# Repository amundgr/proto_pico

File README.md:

# proto_pico
A mash of several different projects in one PCB in an attempt to kickstart all of them at once. Why fail and give up on one project when you can do it on several at once!

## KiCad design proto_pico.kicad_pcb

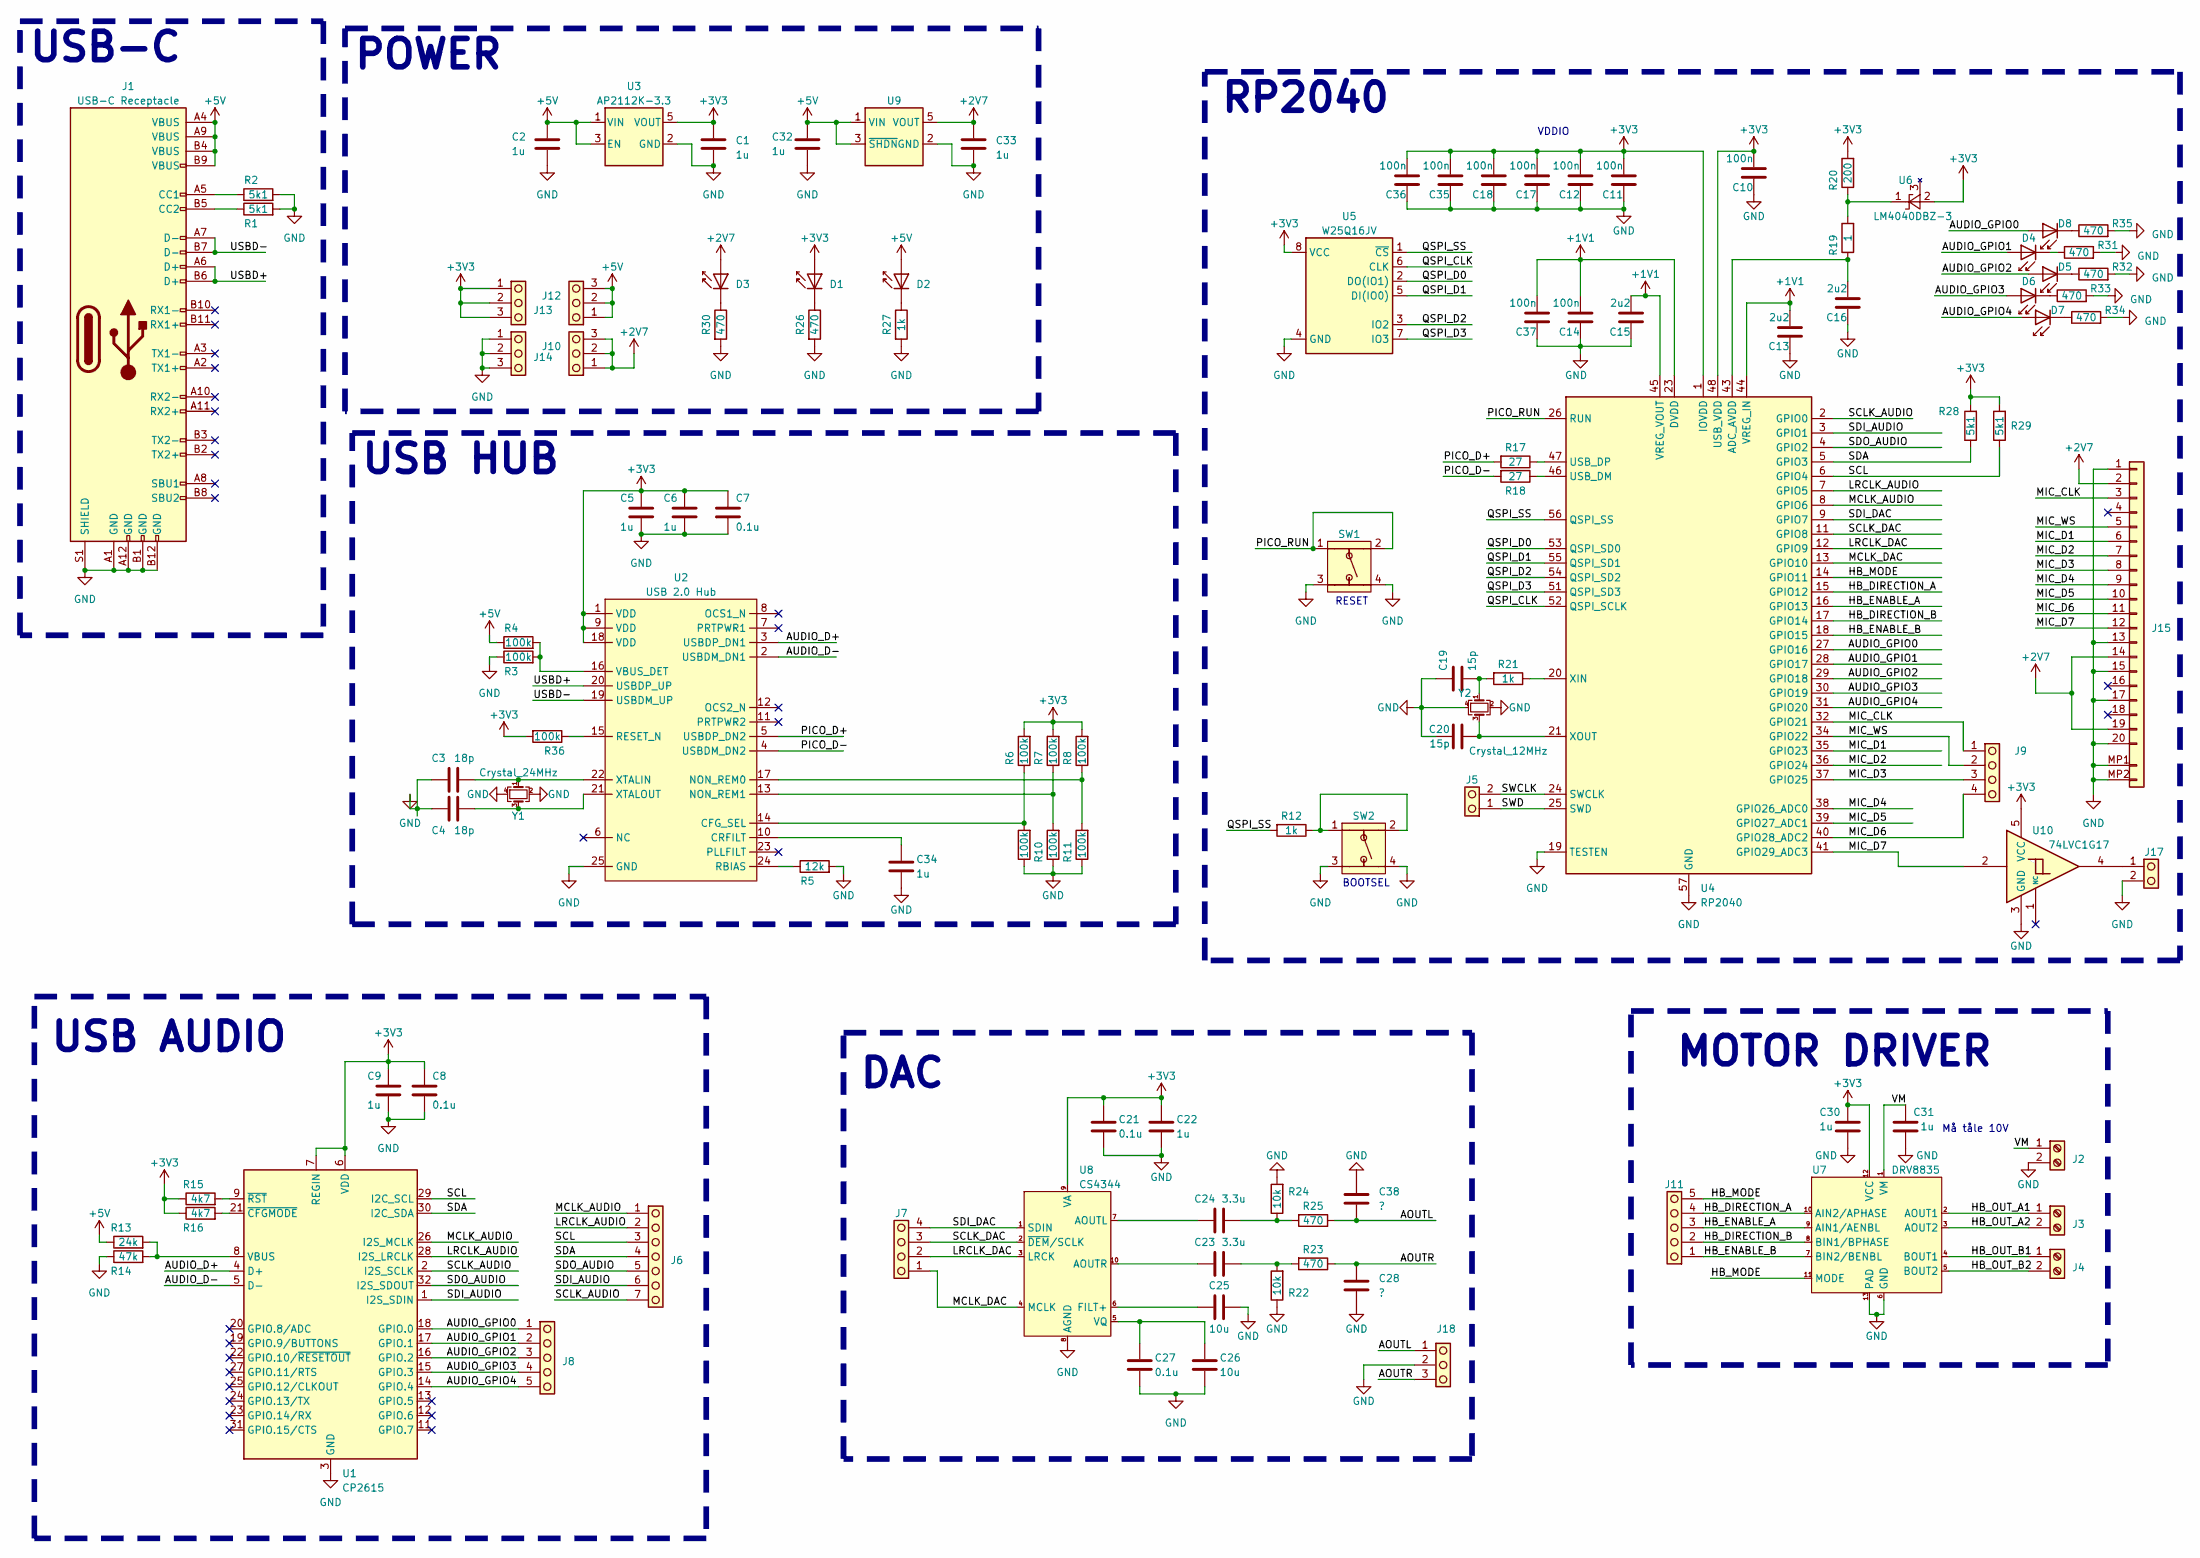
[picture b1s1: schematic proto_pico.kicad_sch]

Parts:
C1, C2, C5, C6, C9, C22, C30, C31, C32, C33, C34: 1u; C_0603_1608Metric
C3, C4: 18p; C_0603_1608Metric
C7, C8, C21, C27: 0.1u; C_0603_1608Metric
C10, C11, C12, C14, C17, C18, C35, C36, C37: 100n; C_0603_1608Metric
C13, C15, C16: 2u2; C_0603_1608Metric
C19, C20: 15p; C_0603_1608Metric
C23, C24: 3.3u; C_0805_2012Metric
C25, C26: 10u; C_0805_2012Metric
C28, C38: ?; C_0805_2012Metric
D1, D2, D3, D4, D5, D6, D7, D8: LED_0603_1608Metric
J1: USB-C Receptacle; USB_C_Receptacle_Amphenol_12401610E4-2A
J2, J3, J4: Screw_Terminal_01x02; 2x1_screw_terminal
J5, J17: PinHeader_1x02_P2.54mm_Vertical
J6: Header_2.54mm_1x7; PinHeader_1x07_P2.54mm_Vertical
J7, J9: PinHeader_1x04_P2.54mm_Vertical
J8, J11: Header_2.54mm_1x5; PinHeader_1x05_P2.54mm_Vertical
J10, J12, J13, J14, J18: PinHeader_1x03_P2.54mm_Vertical
J15: FFC_20_Pin
R1, R2, R28, R29: 5k1; R_0603_1608Metric
R3, R4, R6, R7, R8, R9, R10, R11, R36: 100k; R_0603_1608Metric
R5: 12k; R_0603_1608Metric
R12, R21, R27: 1k; R_0603_1608Metric
R13: 24k; R_0603_1608Metric
R14: 47k; R_0603_1608Metric
R15, R16: 4k7; R_0603_1608Metric
R17, R18: 27; R_0603_1608Metric
R19: 1; R_0603_1608Metric
R20: 200; R_0603_1608Metric
R22, R24: 10k; R_0603_1608Metric
R23, R25, R26, R30, R31, R32, R33, R34, R35: 470; R_0603_1608Metric
SW1, SW2: PTS647
U1: CP2615; QFN-32-1EP_5x5mm_P0.5mm_EP3.3x3.3mm
U2: USB 2.0 Hub; QFN-24-1EP_4x4mm_P0.5mm_EP2.5x2.5mm
U3: AP2112K-3.3; SOT-23-5
U4: RP2040; QFN-56-1EP_7x7mm_P0.4mm_EP3.2x3.2mm
U5: W25Q16JV; SOIC-8_5.23x5.23mm_P1.27mm
U6: LM4040DBZ-3; SOT-23-3
U7: DRV8835; WSON-12-1EP_3x2mm_P0.5mm_EP1x2.65
U8: CS4344; MSOP-10_3x3mm_P0.5mm
U9: SOT-23-5
U10: 74LVC1G17; SOT-23-5
Y1: Crystal_24MHz; Crystal_SMD_SeikoEpson_FA128-4Pin_2.0x1.6mm
Y2: Crystal_12MHz; ECX-32

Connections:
+1V1: C13.2, C14.2, C15.2, C37.2, U4.23 (DVDD), U4.44 (VREG_IN), U4.45 (VREG_VOUT), U4.50 (DVDD)
+2V8: C33.1, D3.2 (A), J10.1, J10.2, J10.3, J15.2, J15.14, J15.19, U9.5 (VOUT)
+3V3: C1.1, C5.1, C6.1, C7.1, C8.1, C9.1, C10.2, C11.2, C12.2, C17.2, C18.2, C21.1, C22.1, C30.1, C35.2, C36.2, D1.2 (A), J13.1, J13.2, J13.3, R6.2, R7.2, R8.2, R15.1, R16.1, R20.2, R28.2, R29.2, R36.2, U1.6 (VDD), U1.7 (REGIN), U2.1 (VDD), U2.9 (VDD), U2.18 (VDD), U3.5 (VOUT), U4.1 (IOVDD), U4.10 (IOVDD), U4.22 (IOVDD), U4.33 (IOVDD), U4.42 (IOVDD), U4.48 (USB_VDD), U4.49 (IOVDD), U5.8 (VCC), U6.2 (A), U7.12 (VCC), U8.9 (VA), U10.5 (VCC)
+5V: C2.1, C32.1, D2.2 (A), J1.A4 (VBUS), J1.A9 (VBUS), J1.B4 (VBUS), J1.B9 (VBUS), J12.1, J12.2, J12.3, R4.1, R13.1, U3.1 (VIN), U3.3 (EN), U9.1 (VIN), U9.3 (~SHDN)
/AOUTL: C38.2, J18.1, R25.1
/AOUTR: C28.1, J18.3, R23.1
/AUDIO_D+: U1.4 (D+), U2.3 (USBDP_DN1)
/AUDIO_D-: U1.5 (D-), U2.2 (USBDM_DN1)
/AUDIO_GPIO0: D8.2 (A), J8.1, U1.18 (GPIO.0), U4.27 (GPIO16)
/AUDIO_GPIO1: D4.2 (A), J8.2, U1.17 (GPIO.1), U4.28 (GPIO17)
/AUDIO_GPIO2: D5.2 (A), J8.3, U1.16 (GPIO.2), U4.29 (GPIO18)
/AUDIO_GPIO3: D6.2 (A), J8.4, U1.15 (GPIO.3), U4.30 (GPIO19)
/AUDIO_GPIO4: D7.2 (A), J8.5, U1.14 (GPIO.4), U4.31 (GPIO20)
/HB_DIRECTION_A: J11.4, U4.15 (GPIO12), U7.10 (AIN2/APHASE)
/HB_DIRECTION_B: J11.2, U4.17 (GPIO14), U7.8 (BIN1/BPHASE)
/HB_ENABLE_A: J11.3, U4.16 (GPIO13), U7.9 (AIN1/AENBL)
/HB_ENABLE_B: J11.1, U4.18 (GPIO15), U7.7 (BIN2/BENBL)
/HB_MODE: J11.5, U4.14 (GPIO11), U7.11 (MODE)
/HB_OUT_A1: J3.1, U7.2 (AOUT1)
/HB_OUT_A2: J3.2, U7.3 (AOUT2)
/HB_OUT_B1: J4.1, U7.4 (BOUT1)
/HB_OUT_B2: J4.2, U7.5 (BOUT2)
/LRCLK_AUDIO: J6.2, U1.28 (I2S_LRCLK), U4.7 (GPIO5)
/LRCLK_DAC: J7.2, U4.12 (GPIO9), U8.3 (LRCK)
/MCLK_AUDIO: J6.1, U1.26 (I2S_MCLK), U4.8 (GPIO6)
/MCLK_DAC: J7.1, U4.13 (GPIO10), U8.4 (MCLK)
/MIC_CLK: J9.1, J15.3, U4.32 (GPIO21)
/MIC_D1: J15.6, U4.35 (GPIO23)
/MIC_D2: J15.7, U4.36 (GPIO24)
/MIC_D3: J9.3, J15.8, U4.37 (GPIO25)
/MIC_D4: J15.9, U4.38 (GPIO26_ADC0)
/MIC_D5: J15.10, U4.39 (GPIO27_ADC1)
/MIC_D6: J9.4, J15.11, U4.40 (GPIO28_ADC2)
/MIC_D7: J15.12, U4.41 (GPIO29_ADC3), U10.2
/MIC_WS: J9.2, J15.5, U4.34 (GPIO22)
/PICO_D+: R17.2, U2.5 (USBDP_DN2)
/PICO_D-: R18.2, U2.4 (USBDM_DN2)
/PICO_RUN: SW1.1, SW1.2, U4.26 (RUN)
/QSPI_CLK: U4.52 (QSPI_SCLK), U5.6 (CLK)
/QSPI_D0: U4.53 (QSPI_SD0), U5.2 (DO(IO1))
/QSPI_D1: U4.55 (QSPI_SD1), U5.5 (DI(IO0))
/QSPI_D2: U4.54 (QSPI_SD2), U5.3 (IO2)
/QSPI_D3: U4.51 (QSPI_SD3), U5.7 (IO3)
/QSPI_SS: R12.2, U4.56 (QSPI_SS), U5.1 (~CS)
/SCL: J6.3, R29.1, U1.29 (I2C_SCL), U4.6 (GPIO4)
/SCLK_AUDIO: J6.7, U1.2 (I2S_SCLK), U4.2 (GPIO0)
/SCLK_DAC: J7.3, U4.11 (GPIO8), U8.2 (~DEM/SCLK)
/SDA: J6.4, R28.1, U1.30 (I2C_SDA), U4.5 (GPIO3)
/SDI_AUDIO: J6.6, U1.1 (I2S_SDIN), U4.3 (GPIO1)
/SDI_DAC: J7.4, U4.9 (GPIO7), U8.1 (SDIN)
/SDO_AUDIO: J6.5, U1.32 (I2S_SDOUT), U4.4 (GPIO2)
/SWCLK: J5.2, U4.24 (SWCLK)
/SWD: J5.1, U4.25 (SWD)
/USBD+: J1.A6 (D+), J1.B6 (D+), U2.20 (USBDP_UP)
/USBD-: J1.A7 (D-), J1.B7 (D-), U2.19 (USBDM_UP)
/VM: C31.1, J2.1, U7.1 (VM)
GND: C1.2, C2.2, C3.1, C4.1, C5.2, C6.2, C7.2, C8.2, C9.2, C10.1, C11.1, C12.1, C13.1, C14.1, C15.1, C16.1, C17.1, C18.1, C19.1, C20.1, C21.2, C22.2, C25.2, C26.2, C27.2, C28.2, C30.2, C31.2, C32.2, C33.2, C34.2, C35.1, C36.1, C37.1, C38.1, J1.A1 (GND), J1.A12 (GND), J1.B1 (GND), J1.B12 (GND), J1.S1 (SHIELD), J2.2, J14.1, J14.2, J14.3, J15.1, J15.13, J15.15, J15.17, J15.20, J15.MP1, J15.MP2, J17.2, J18.2, R1.2, R2.2, R3.1, R5.2, R9.1, R10.1, R11.1, R14.1, R22.1, R24.2, R26.2, R27.2, R30.2, R31.2, R32.2, R33.2, R34.2, R35.2, SW1.3, SW1.4, SW2.3, SW2.4, U1.3 (GND), U1.33 (GND), U2.25 (GND), U3.2 (GND), U4.19 (TESTEN), U4.57 (GND), U5.4 (GND), U7.6 (GND), U7.13 (PAD), U8.8 (AGND), U9.2 (GND), U10.3 (GND), Y1.2, Y1.4, Y2.2, Y2.4
unnamed: C19.2, R21.2, Y2.1
unnamed: C23.2, R22.2, R23.2
unnamed: C24.1, R24.1, R25.2
unnamed: D1.1 (K), R26.1
unnamed: D2.1 (K), R27.1
unnamed: D3.1 (K), R30.1
unnamed: D4.1 (K), R31.1
unnamed: D5.1 (K), R32.1
unnamed: D6.1 (K), R33.1
unnamed: D7.1 (K), R34.1
unnamed: D8.1 (K), R35.1
unnamed: J1.A5 (CC1), R2.1
unnamed: J1.B5 (CC2), R1.1
unnamed: J17.1, U10.4
unnamed: R12.1, SW2.1, SW2.2
unnamed: R13.2, R14.2, U1.8 (VBUS)
unnamed: R16.2, U1.21 (~CFGMODE)
unnamed: R15.2, U1.9 (~RST)
unnamed: R6.1, R9.2, U2.14 (CFG_SEL)
unnamed: C34.1, U2.10 (CRFILT)
unnamed: R8.1, R11.2, U2.17 (NON_REM0)
unnamed: R7.1, R10.2, U2.13 (NON_REM1)
unnamed: R5.1, U2.24 (RBIAS)
unnamed: R36.1, U2.15 (RESET_N)
unnamed: R3.2, R4.2, U2.16 (VBUS_DET)
unnamed: C3.2, U2.22 (XTALIN), Y1.1
unnamed: C4.2, U2.21 (XTALOUT), Y1.3
unnamed: C16.2, R19.1, U4.43 (ADC_AVDD)
unnamed: R18.1, U4.46 (USB_DM)
unnamed: R17.1, U4.47 (USB_DP)
unnamed: R21.1, U4.20 (XIN)
unnamed: C20.2, U4.21 (XOUT), Y2.3
unnamed: R19.2, R20.1, U6.1 (K)
unnamed: C24.2, U8.7 (AOUTL)
unnamed: C23.1, U8.10 (AOUTR)
unnamed: C25.1, U8.6 (FILT+)
unnamed: C26.1, C27.1, U8.5 (VQ)

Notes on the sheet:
USB AUDIO
VDDIO
DAC
BOOTSEL
RESET
POWER
USB-C
Må tåle 10V
USB HUB
MOTOR DRIVER
RP2040

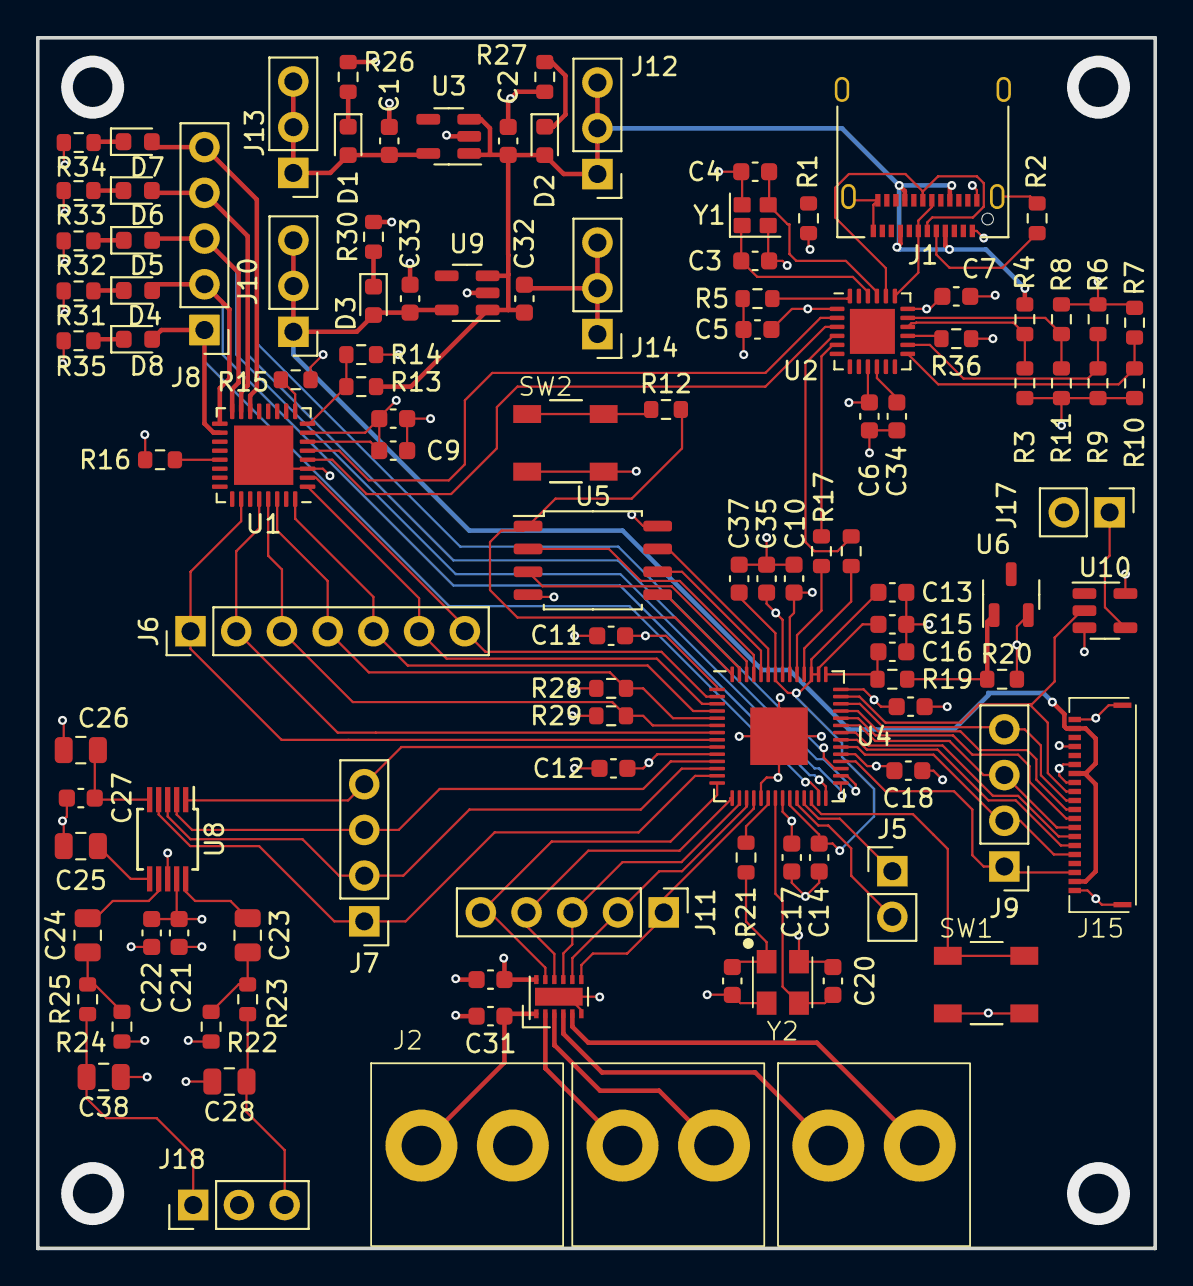
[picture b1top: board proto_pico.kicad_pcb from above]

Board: 4 copper layers, 62.1 x 67.3 mm, 112 parts (0 on the bottom side), 94 nets.

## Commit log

2023-05-24 current progress
2023-05-24 Update README.md
    FIxed typo in REAMDE.md
2023-05-31 add library tables to git ignore
2023-05-31 add library tables to git ignore, again
2023-05-31 done some routing
2023-06-20 some updates to schematic and component placement
2023-06-21 routing done, DRC left
2023-08-14 add output files
2023-08-14 update to pcb
2023-08-16 forgot to save before pushing last time
